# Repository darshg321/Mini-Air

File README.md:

# Mini-Air

Mini-Air is a DIY FPV drone!
it features:
- a custom flight controller supporting Betaflight
- an ESC supporting Bluejay firmware
- ELRS protocol
- an analog camera
- GPS

the custom flight controller has an on-board OSD, IMU, Barometer, and SPI Flash

i made this project to learn how flight controllers and drones work, and because i want to fly a cool fpv drone. the project is optimized to support the features of all the latest fpv software available. all components are analog to reduce latency, and because 480p drone video with osd in general is really aesthetic. with a 2s lipo and a 2-inch propellers, it leans heavily towards speed rather than range or flight time. the vtx, gps, reciever, and esc are all modular, and so can be swapped with different parts if needed. note that the CAD is simplified to just show the rough connection, i am using a bought frame which will allow for screwing in components.

## Poster (Zine)

## Flight Controller Render

## CAD Render

## PCB

## Schematic

## CAD

https://cad.onshape.com/documents/986fb99af7814b930792b89c/w/8ba981f62ca8b18288746bfa/e/dd69b1ef7cccc17bc086fed8?renderMode=0&uiState=6a3726ba5f00d66196d8cb0d

## Assembly:

1. mount ESC and FC to frame and screw in
2. mount propeller to motor and screw in to frame
3. solder camera, vtx, gps, reciever to flight controller
4. mount camera to front of frame, screw in other components to the back
5. flash betaflight firmware by connecting to FC with a STLINK
6. connect battery and radio controller
7. fly!

## BOM

|Item:                                       |Link:                                                                          |Price (CAD):|FIELD4|FIELD5 |Weight (g)|
|--------------------------------------------|-------------------------------------------------------------------------------|------------|------|-------|----------|
|FC PCB                                      |                                                                               |2.83        |      |       |3.9       |
|FC PCBA                                     |                                                                               |236.5       |      |       |          |
|Frame                                       |https://epicfpv.ca/products/hglrc-talon-frame-black                            |45.31       |      |       |46        |
|AneegFpv 45A ESC                            |https://www.aliexpress.com/item/1005009952151526.html                          |32.99       |      |       |13        |
|4x HappyModel EX1103S 1103 7000KV           |https://www.aliexpress.com/item/1005006105578345.html                          |44.59       |      |       |15.2      |
|Propellers                                  |https://www.aliexpress.com/item/1005006966517627.html                          |6.49        |      |       |3.52      |
|CADDX Ant FPV Lite Camera                   |https://www.aliexpress.com/item/1005009014299964.html                          |19.87       |      |       |2         |
|Zeus nano 350mW VTX                         |https://www.aliexpress.com/item/1005008558004179.html                          |35.58       |      |       |2.4       |
|Foxeer Lollipop 3 Micro Omni V4 RHCP Antenna|https://www.aliexpress.com/item/4001191873858.html                             |16.89       |      |       |4.7       |
|HappyModel 2.4G ELRS EP2 Reciever           |https://www.aliexpress.com/item/1005009851731060.html                          |19.18       |      |       |0.41      |
|NewBeeDrone M10Q Micro GPS Module           |https://newbeedrone.com/products/newbeedrone-m10q-micro-gps-module-with-compass|27.80       |      |       |2.61      |
|LiteRadio 2 ELRS                            |https://www.aliexpress.com/item/1005011890268150.html                          |31.18       |      |       |          |
|x4 2S 450mAh 80C lipo battery               |https://www.aliexpress.com/item/1005006138925891.html                          |37.99       |      |       |30        |
|                                            |                                                                               |            |      |       |          |
|                                            |Total USD                                                                      |401.18      |      |Weight:|123.74    |

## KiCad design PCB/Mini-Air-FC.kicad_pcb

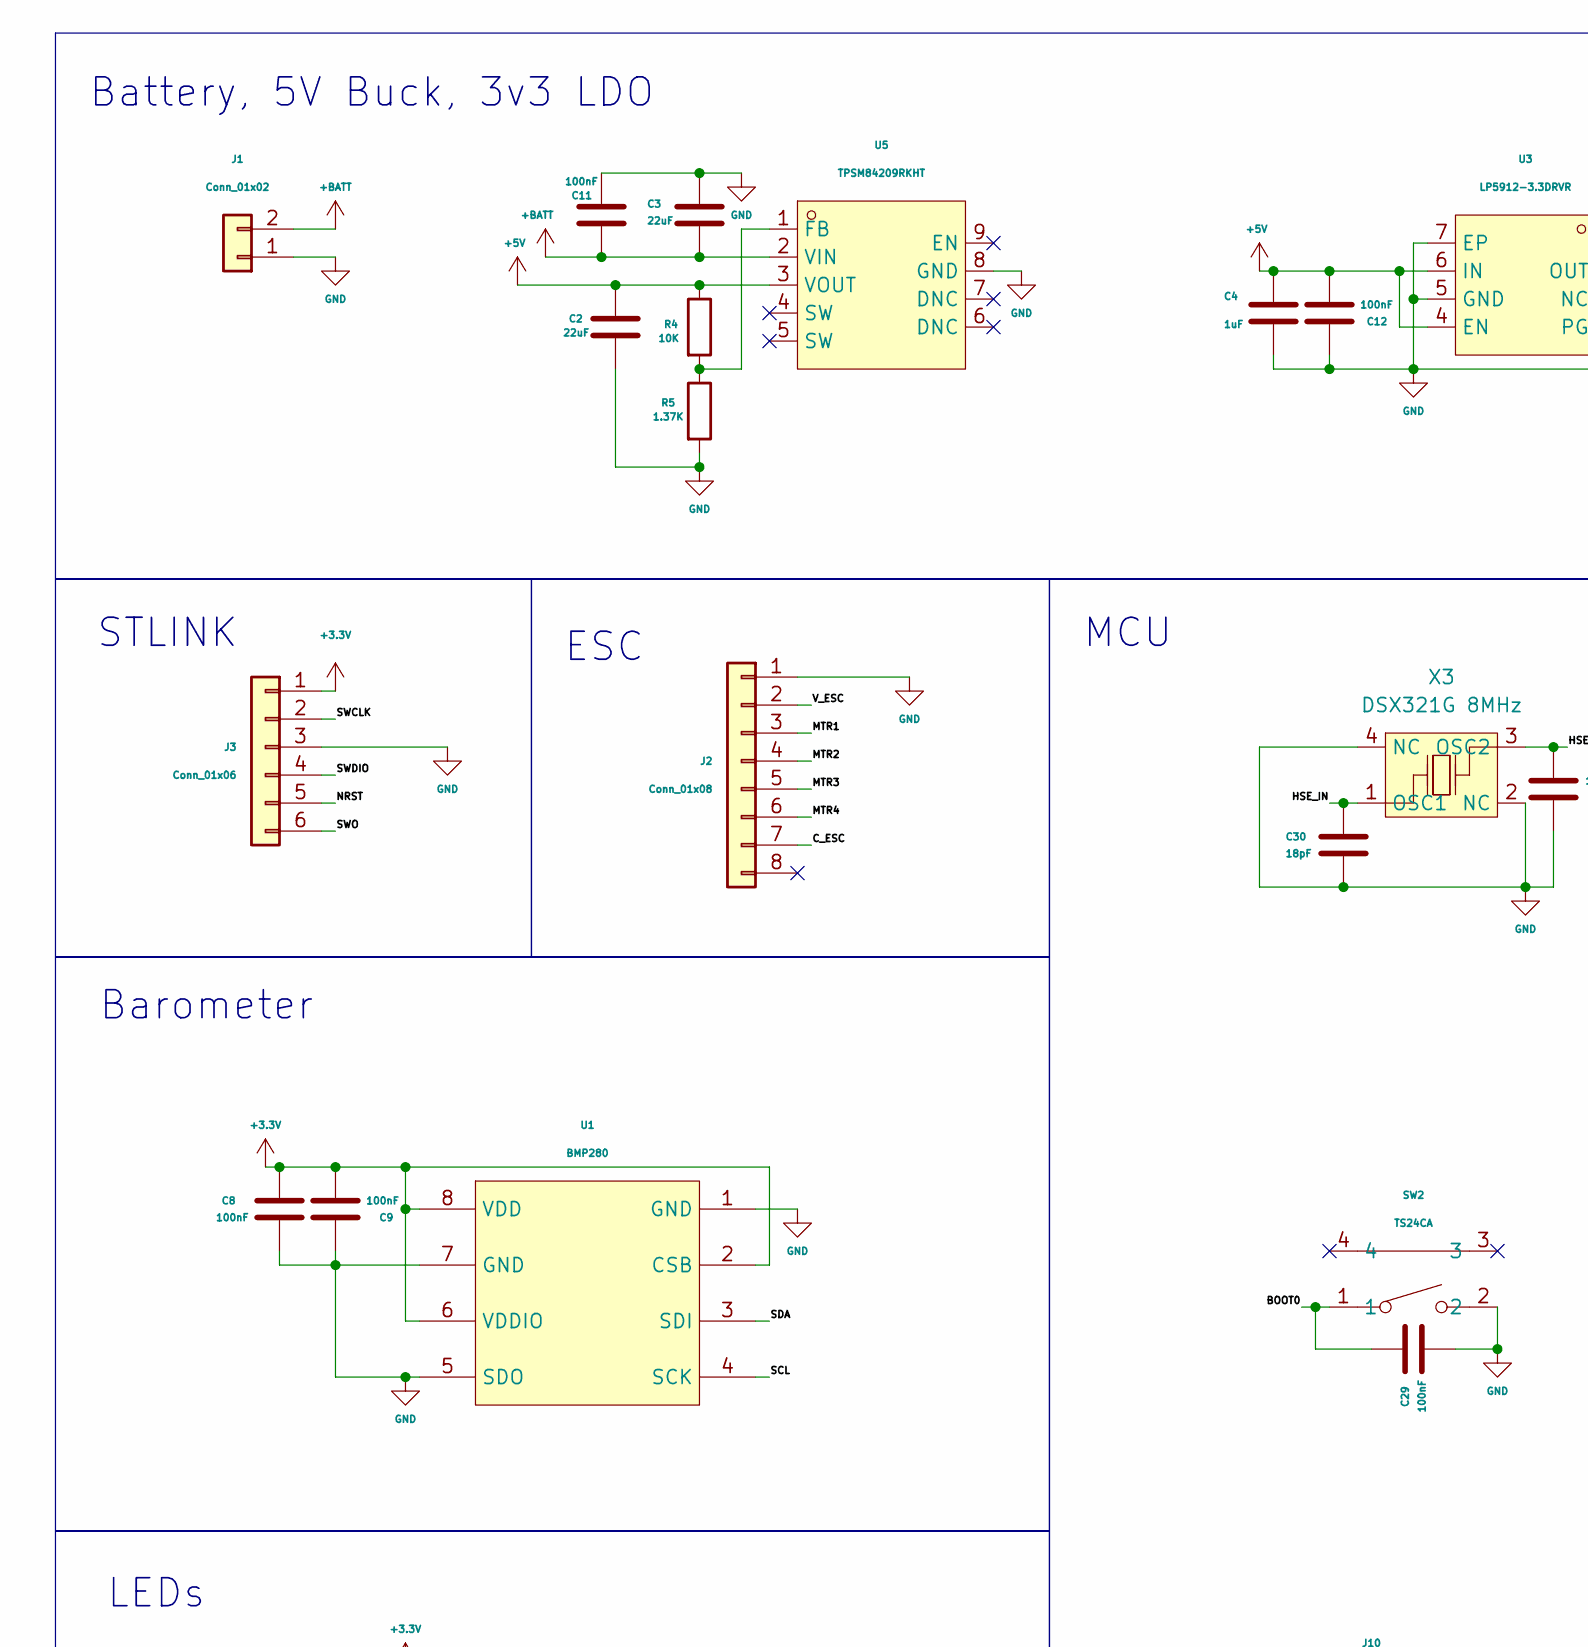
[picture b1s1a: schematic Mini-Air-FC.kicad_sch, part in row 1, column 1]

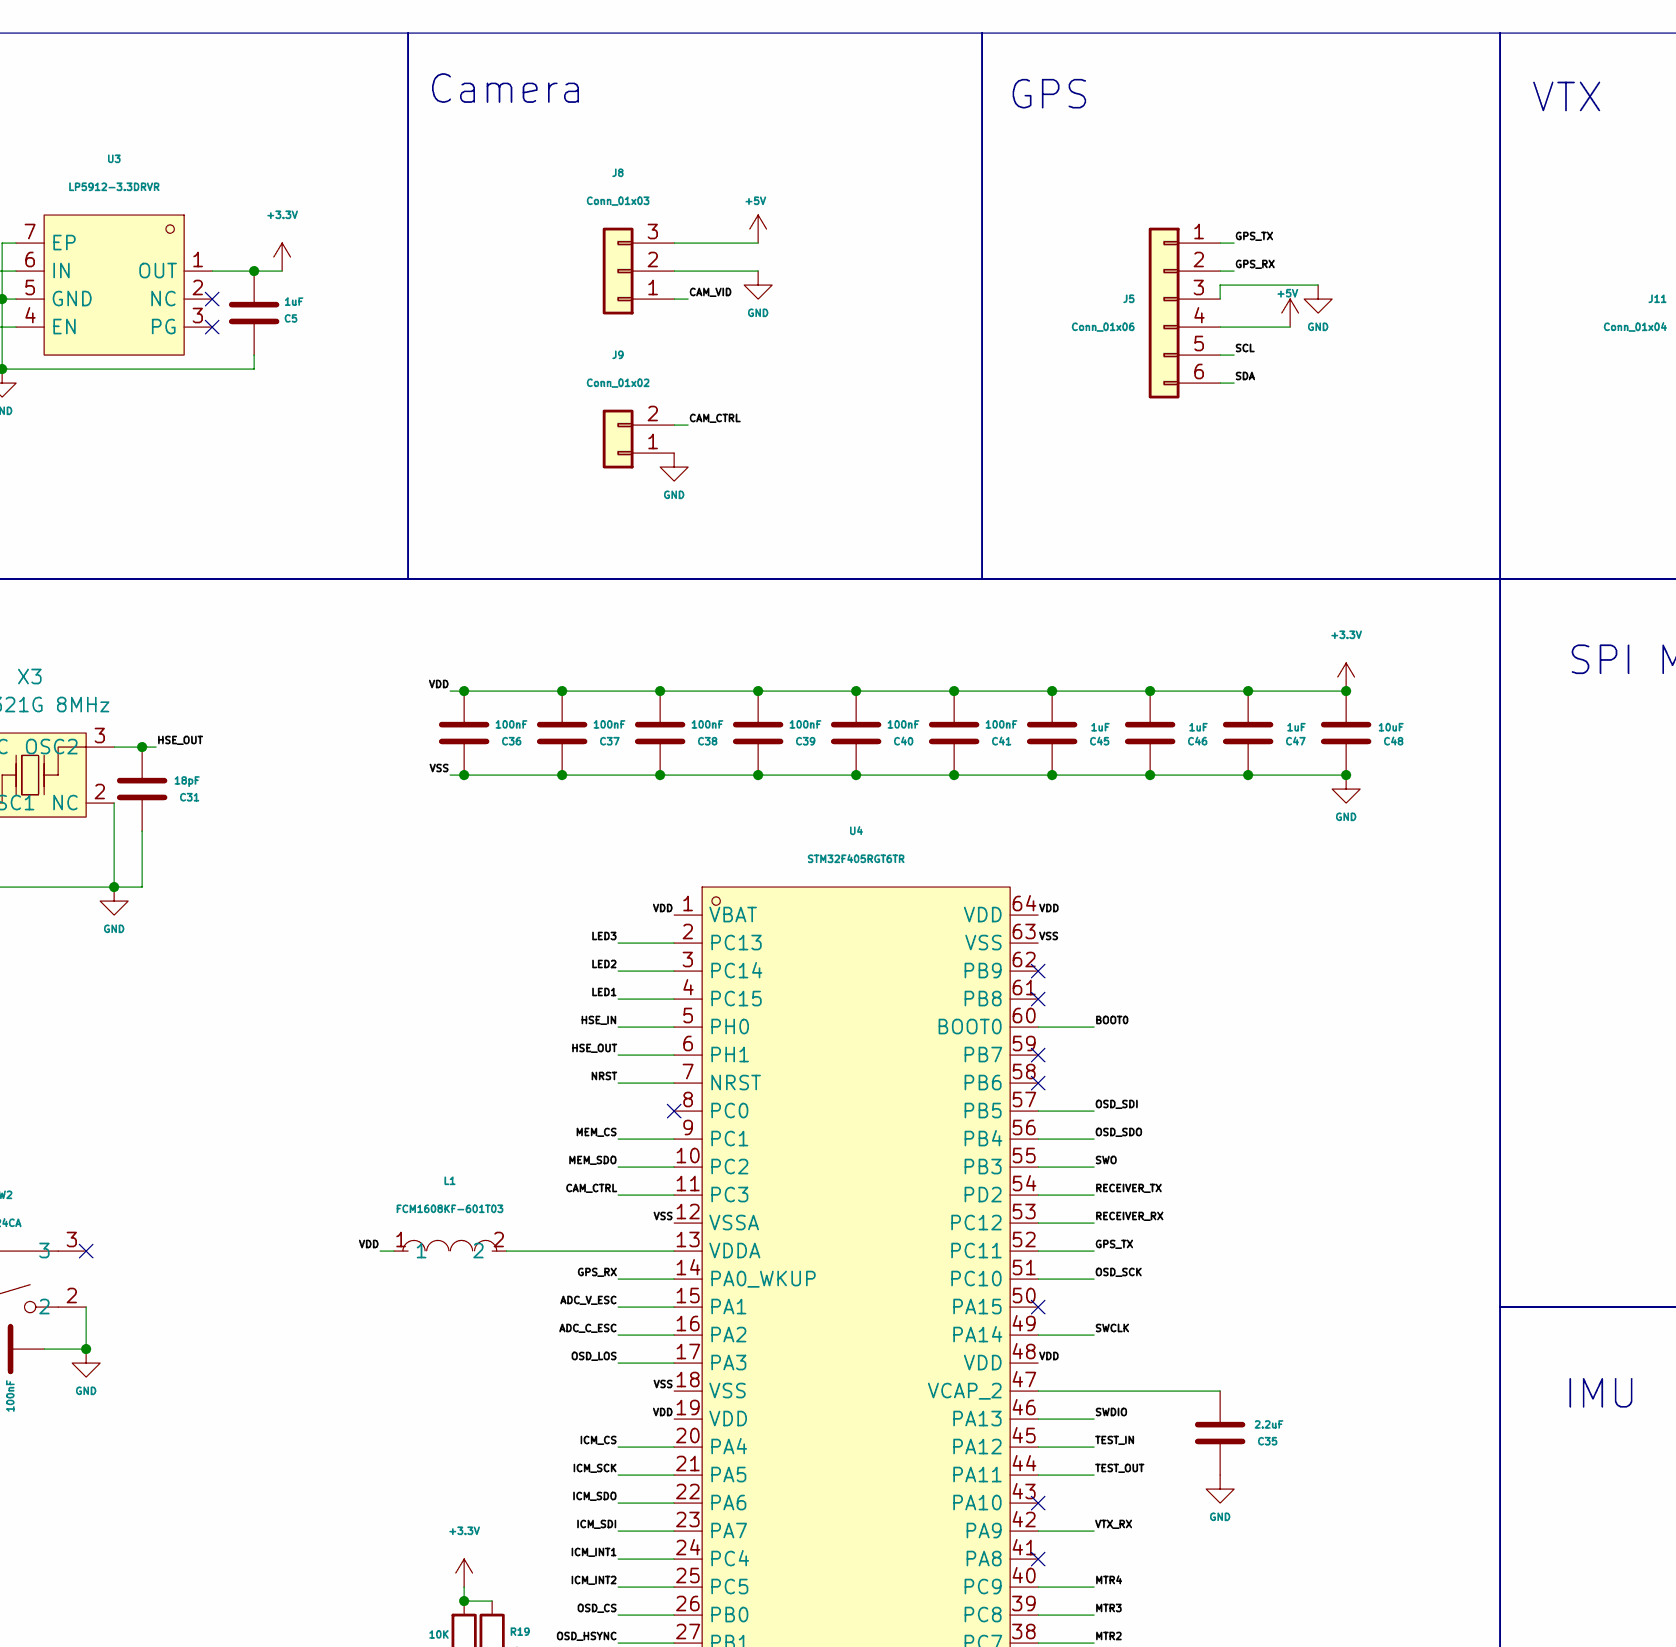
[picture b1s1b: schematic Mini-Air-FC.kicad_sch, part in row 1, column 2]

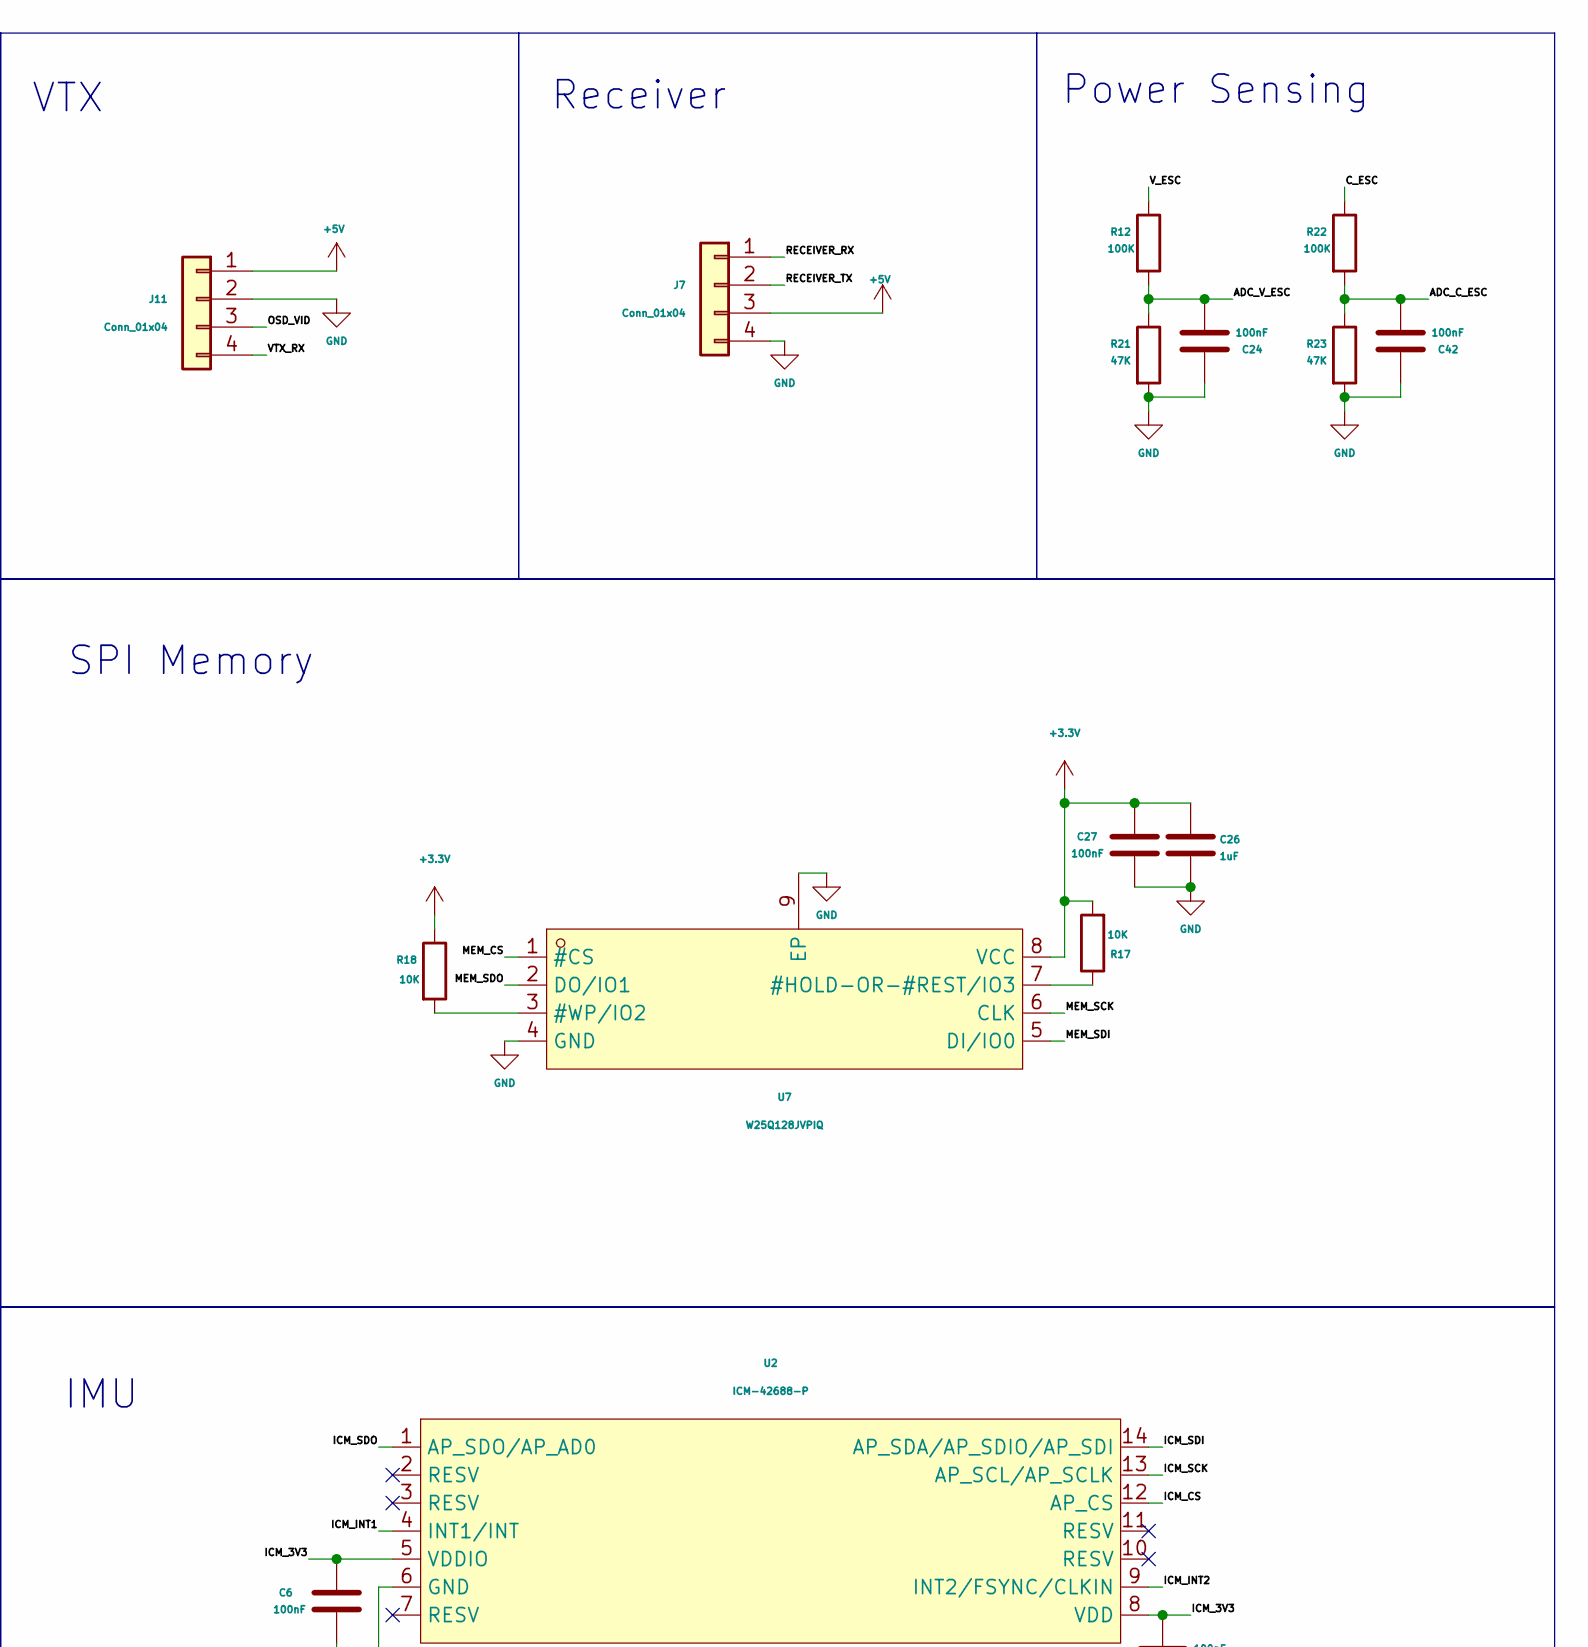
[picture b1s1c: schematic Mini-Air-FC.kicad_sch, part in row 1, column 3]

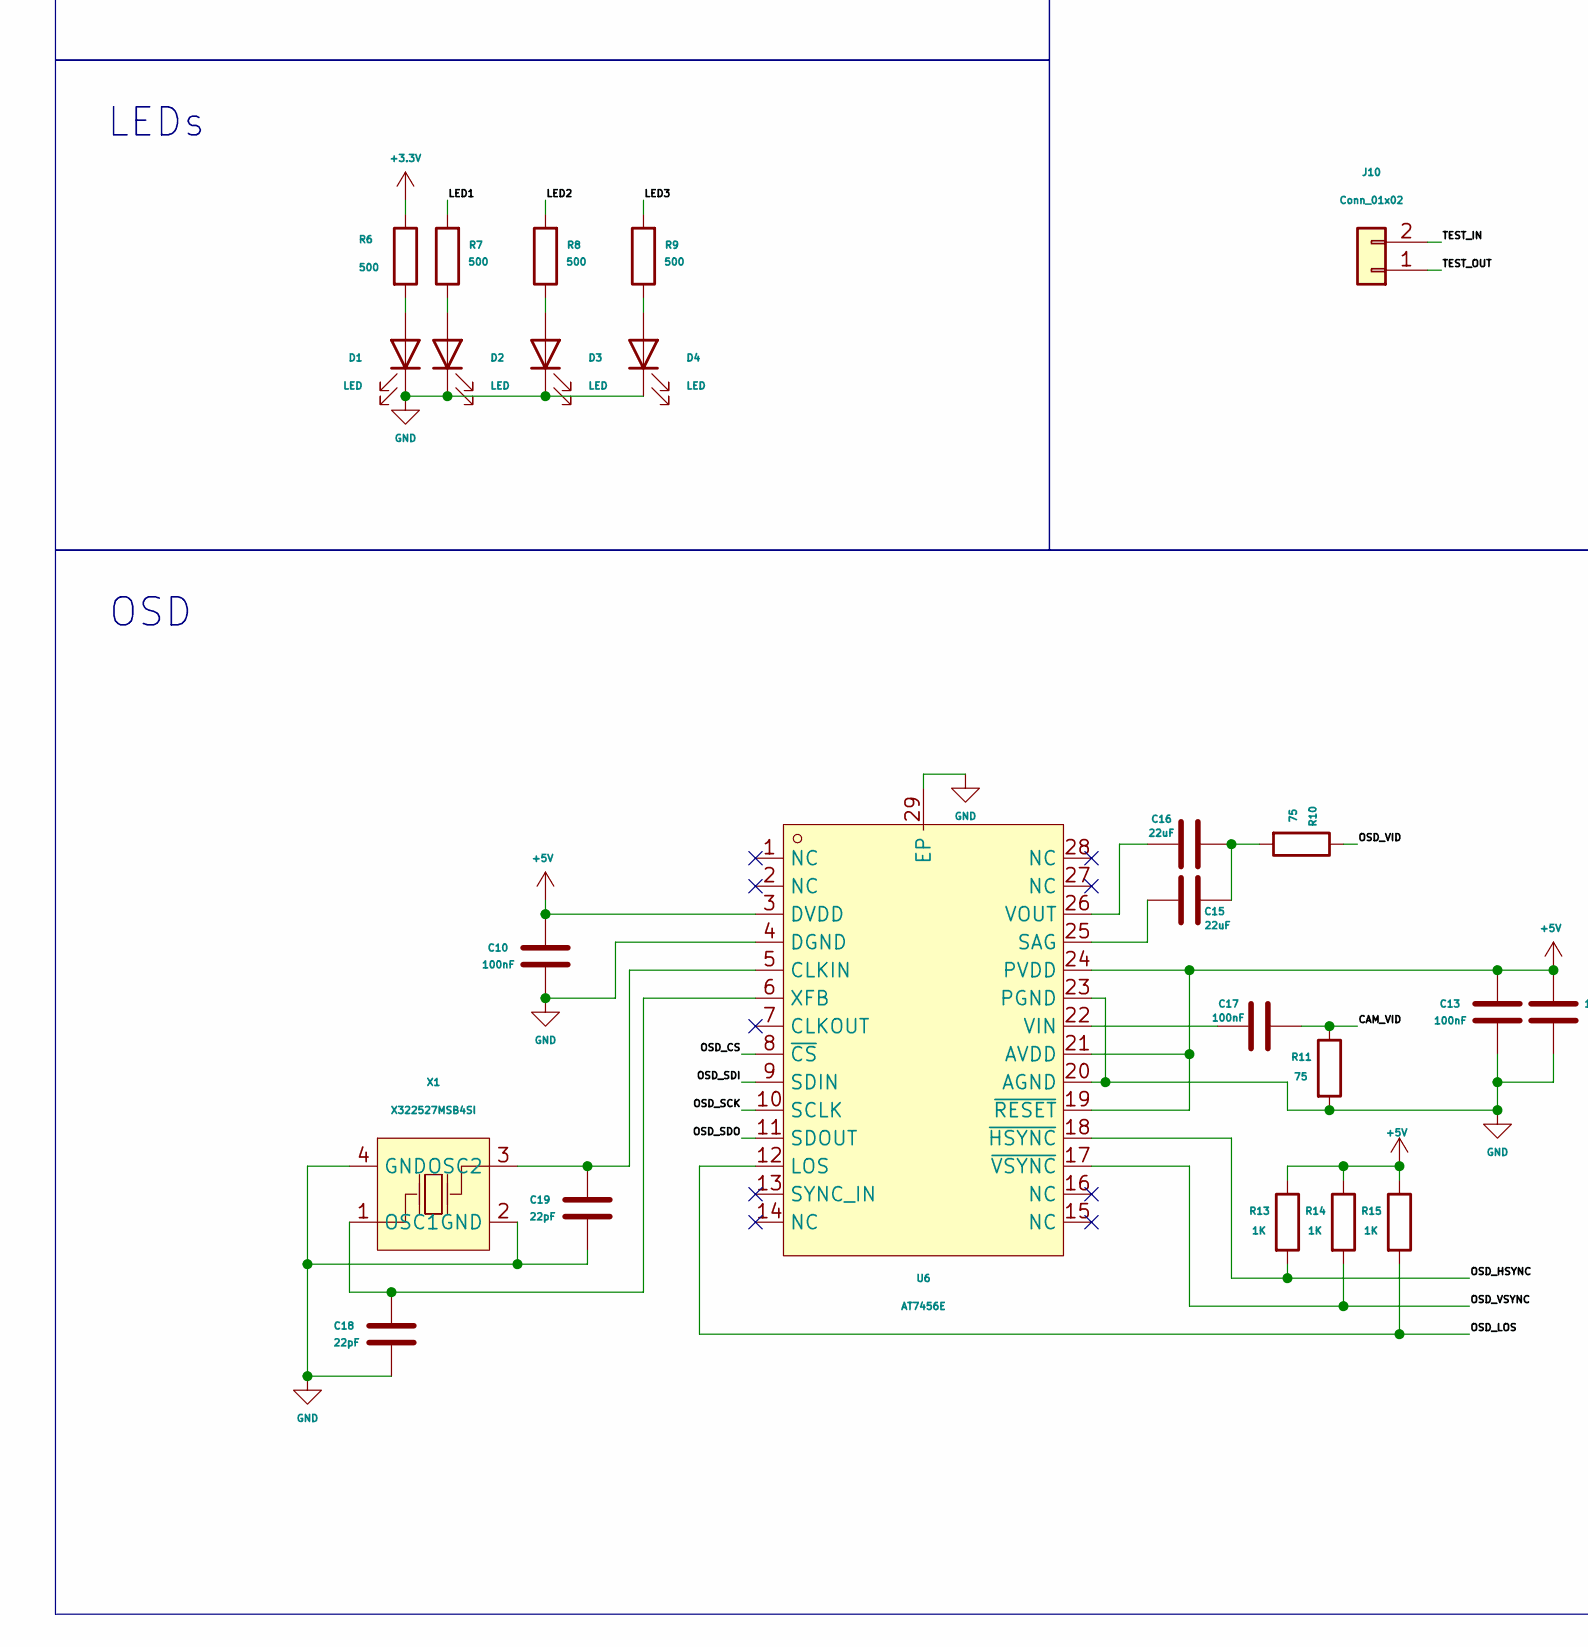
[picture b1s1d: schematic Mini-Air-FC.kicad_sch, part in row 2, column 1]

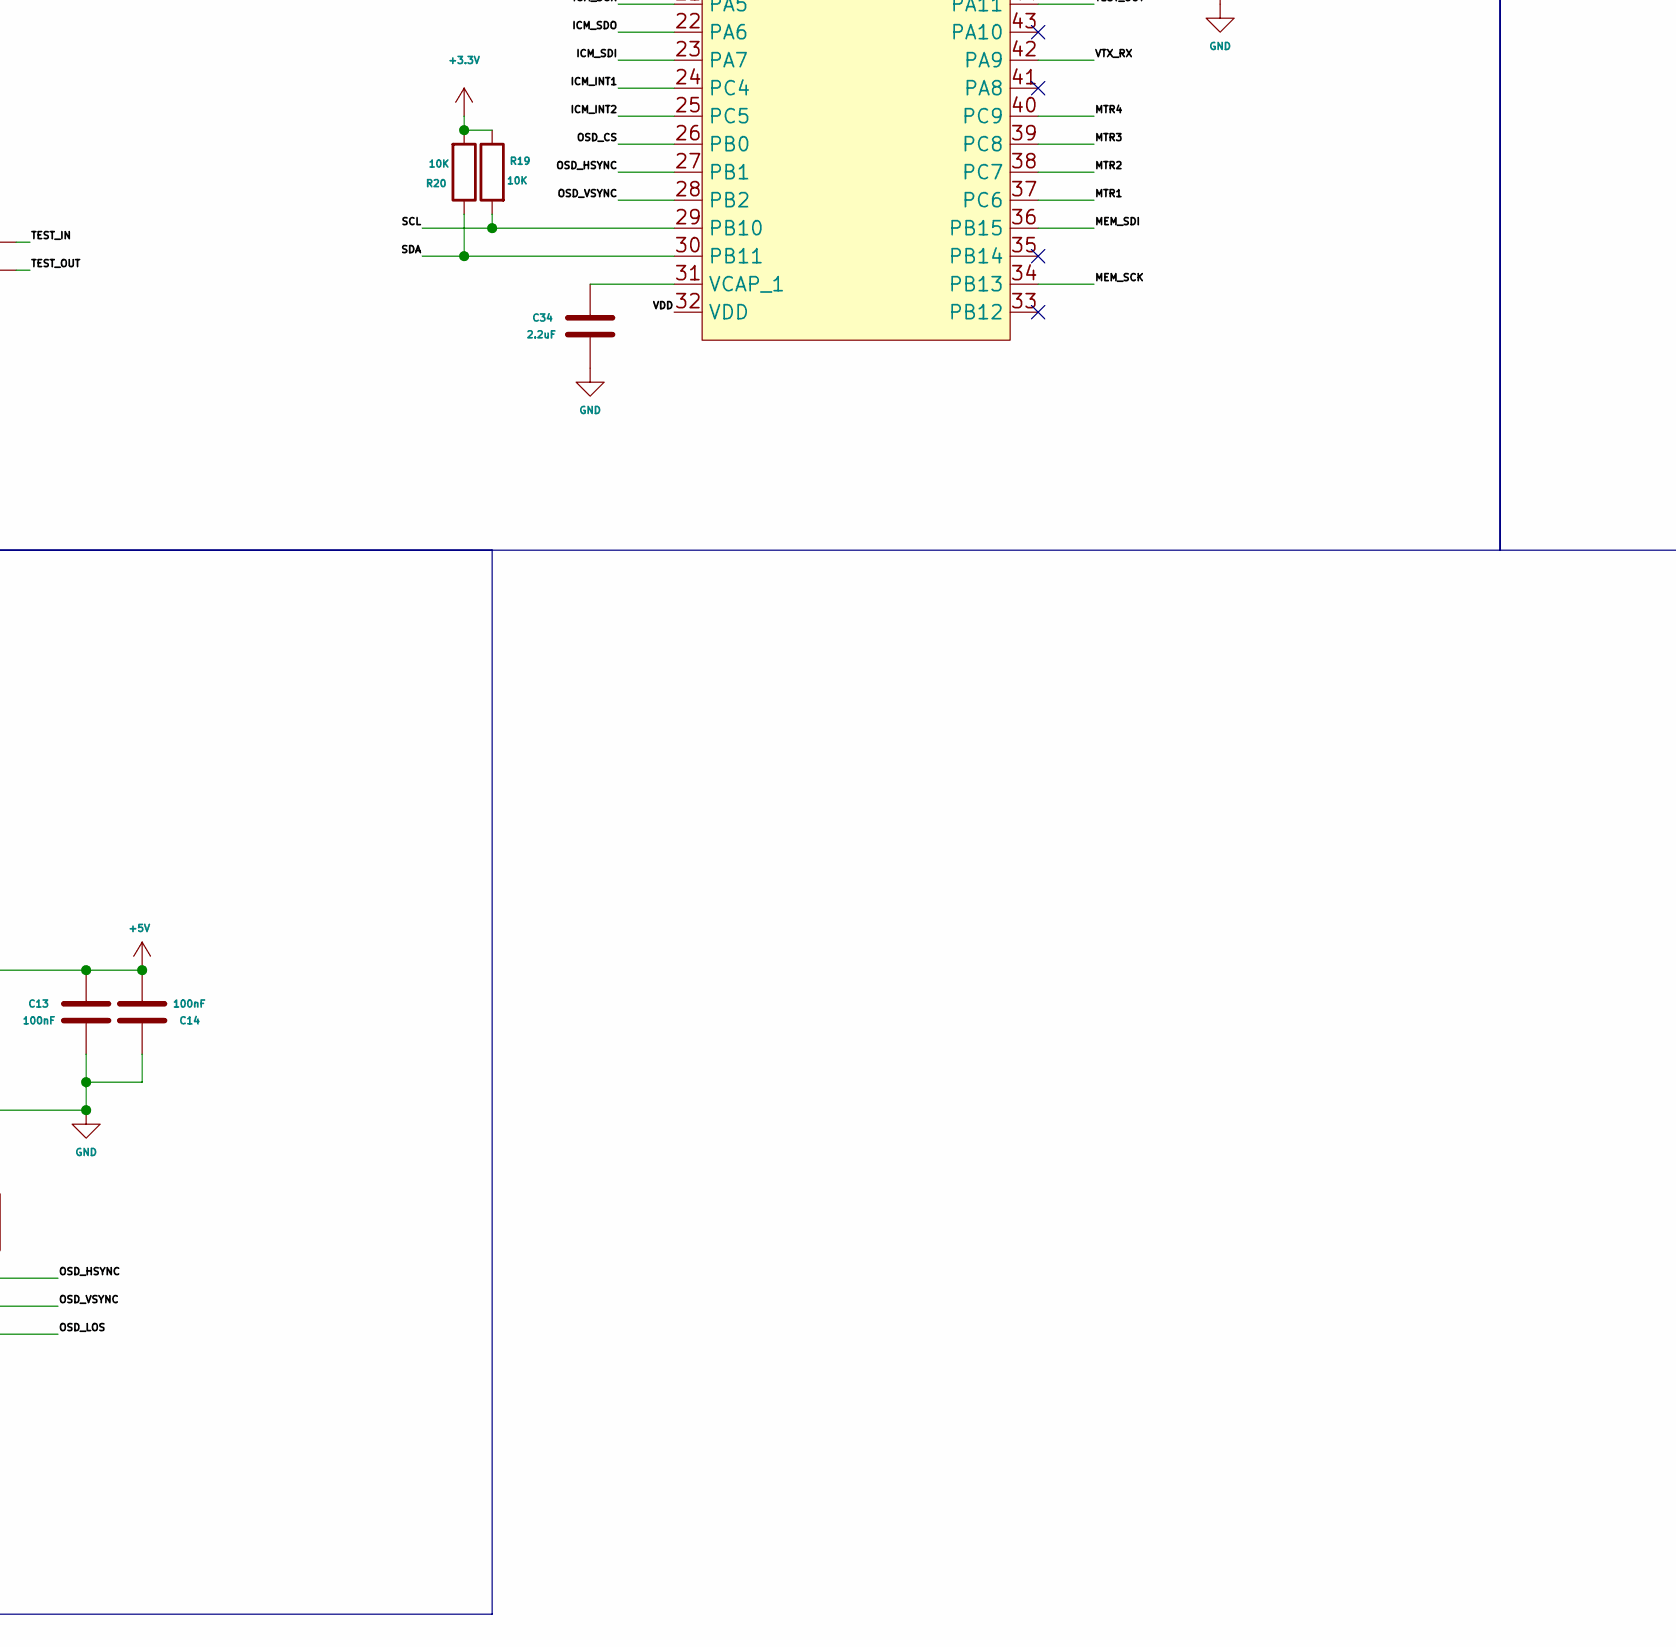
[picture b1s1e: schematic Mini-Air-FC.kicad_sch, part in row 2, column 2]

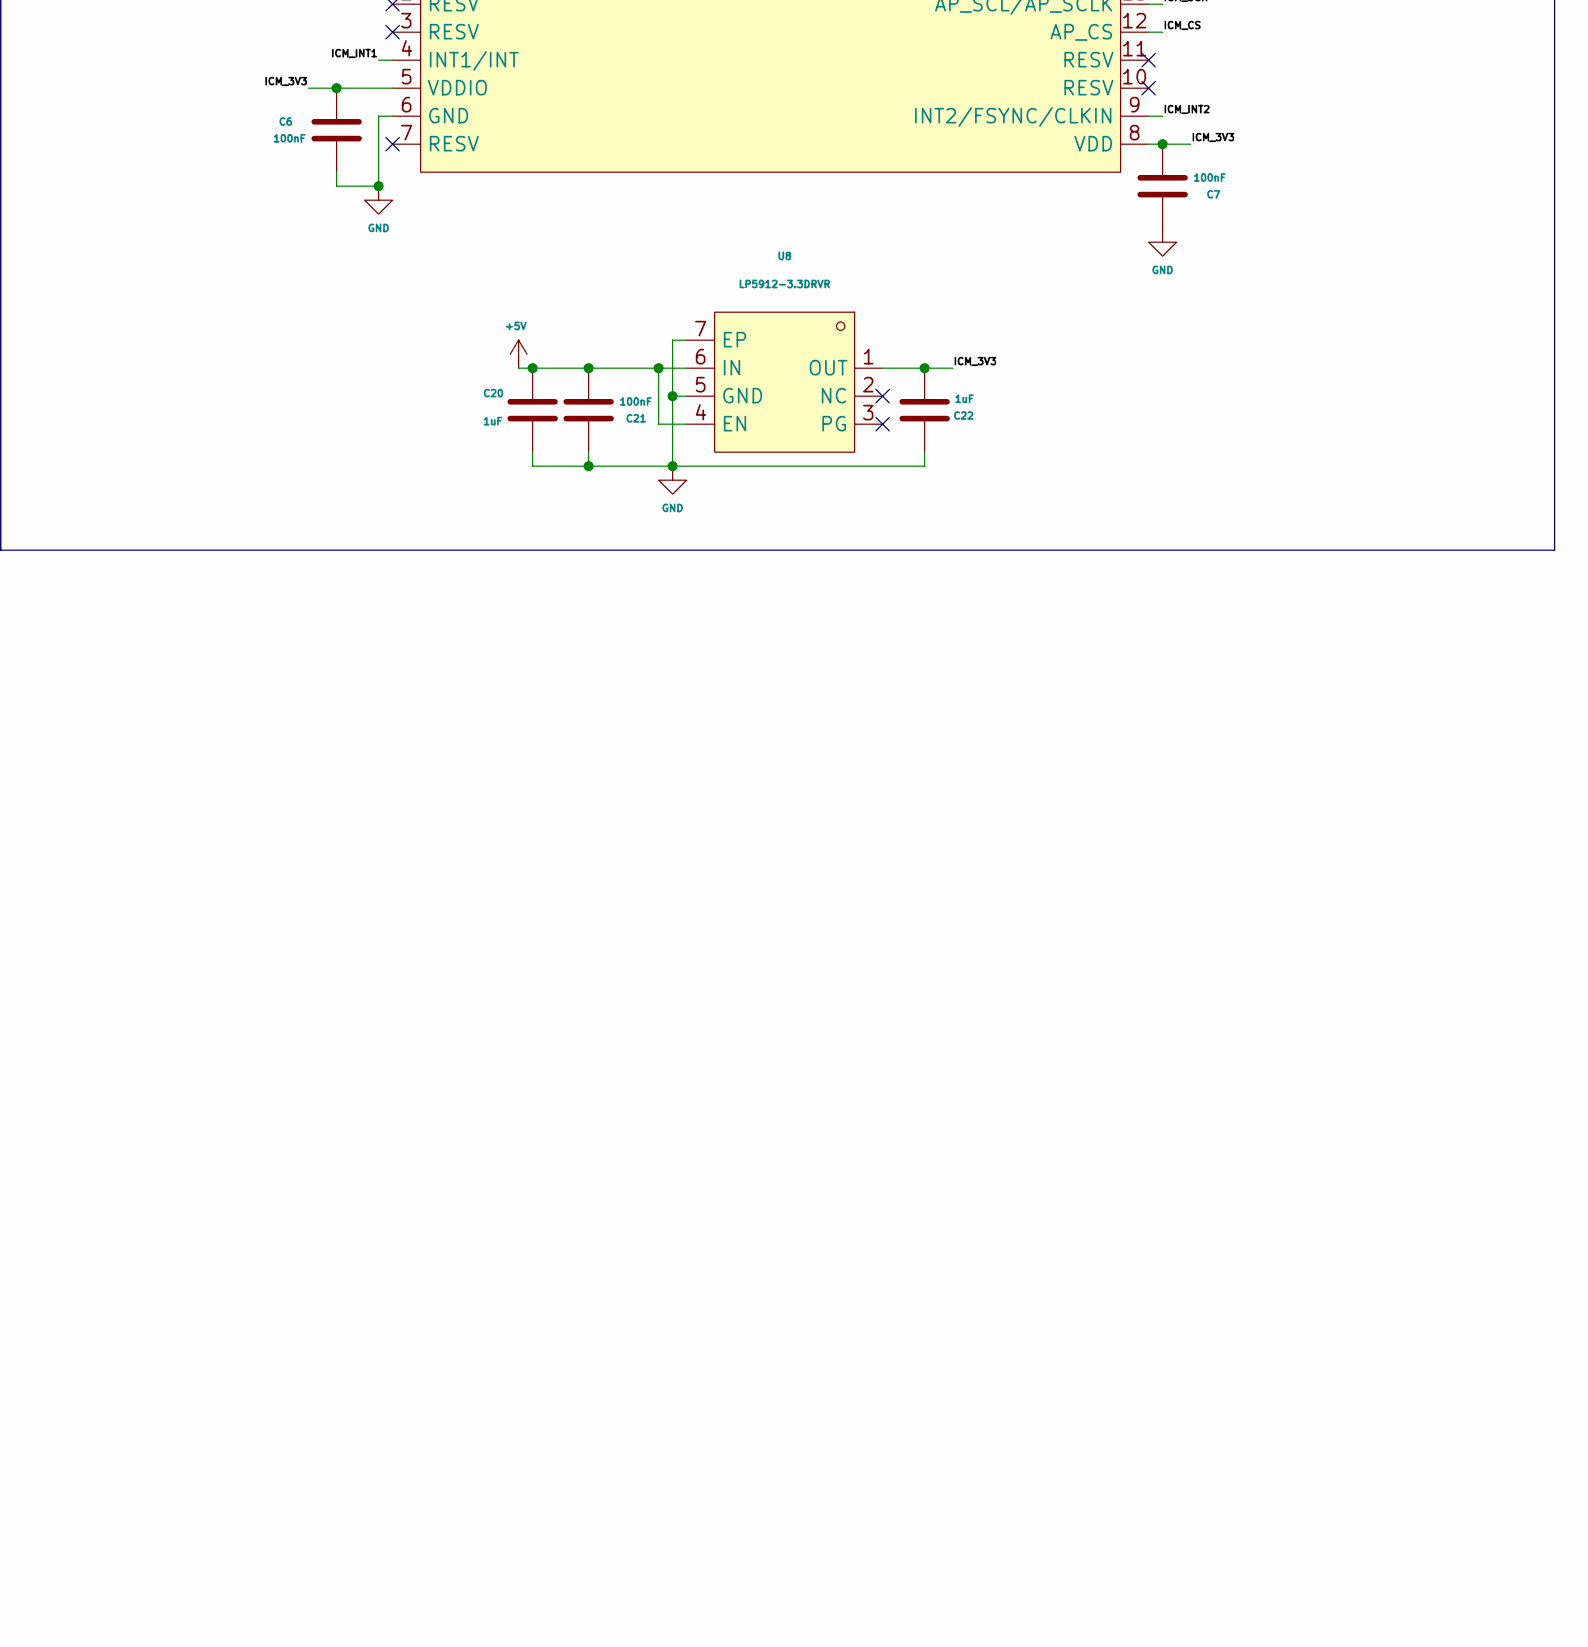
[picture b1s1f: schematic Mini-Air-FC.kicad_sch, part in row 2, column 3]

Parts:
C2, C3, C15, C16: 22uF; C_0805_2012Metric
C4, C5, C20, C22, C26, C45, C46, C47: 1uF; C_0402_1005Metric
C6, C7, C8, C9, C10, C11, C12, C13, C14, C17, C21, C24, C27, C29, C36, C37, C38, C39, C40, C41, C42: 100nF; C_0201_0603Metric
C18, C19: 22pF; C_0201_0603Metric
C30, C31: 18pF; C_0201_0603Metric
C34, C35: 2.2uF; C_0402_1005Metric
C48: 10uF; C_0805_2012Metric
D1, D2, D3, D4: LED; LED_0402_1005Metric
J1, J9, J10: Conn_01x02; PinHeader_1x02_P1.00mm_Vertical
J2: Conn_01x08; JST_SH_SM08B-SRSS-TB_1x08-1MP_P1.00mm_Horizontal
J3, J5: Conn_01x06; PinHeader_1x06_P1.00mm_Vertical
J7, J11: Conn_01x04; PinHeader_1x04_P1.00mm_Vertical
J8: Conn_01x03; PinHeader_1x03_P1.00mm_Vertical
L1: FCM1608KF-601T03; L0603; MPN FCM1608KF-601T03; LCSC Part C141723
R4, R17, R18, R19, R20: 10K; R_0201_0603Metric
R5: 1.37K; R_0201_0603Metric
R6, R7, R8, R9: 500; R_0201_0603Metric
R10, R11: 75; R_0201_0603Metric
R12, R22: 100K; R_0201_0603Metric
R13, R14, R15: 1K; R_0201_0603Metric
R21, R23: 47K; R_0201_0603Metric
SW2: TS24CA; SW-SMD_2P-TS24CA; MPN TS24CA; LCSC Part C393942
U1: BMP280; LGA-8_L2.5-W2.0-P0.65_AMP6127; MPN BMP280; LCSC Part C83291
U2: ICM-42688-P; LGA-14_L3.0-W2.5-P0.50-TL; MPN ICM-42688-P; LCSC Part C1850418
U3, U8: LP5912-3.3DRVR; WSON-6_L2.0-W2.0-P0.65-TL-EP; MPN LP5912-3.3DRVR; LCSC Part C524780
U4: STM32F405RGT6TR; LQFP-64_L10.0-W10.0-P0.50-LS12.0-BL; MPN STM32F405RGT6TR; LCSC Part C2054141
U5: TPSM84209RKHT; QFN-9_L4.4-W4.0-P0.85-YTL; MPN TPSM84209RKHT; LCSC Part C2836944
U6: AT7456E; TSSOP-28_L9.7-W4.4-P0.65-LS6.4-BL-EP-2; MPN AT7456E; LCSC Part C82351
U7: W25Q128JVPIQ; WSON-8_L6.0-W5.0-P1.27-BL-EP; MPN W25Q128JVPIQ; LCSC Part C190862
X1: X322527MSB4SI; CRYSTAL-SMD_4P-L3.2-W2.5-BL-1; MPN X322527MSB4SI; LCSC Part C9008
X3: DSX321G 8MHz; CRYSTAL-SMD_4P-L3.2-W2.5-BL-1; MPN 1C208000BC0R; LCSC Part C57131

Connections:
+3.3V: C5.2, C8.1, C9.2, C26.1, C27.1, C36.2, C37.2, C38.2, C39.2, C40.2, C41.2, C45.2, C46.2, C47.2, C48.2, J3.1, L1.1, R6.1, R17.2, R18.1, R19.1, R20.2, U1.2 (CSB), U1.6 (VDDIO), U1.8 (VDD), U3.1 (OUT), U4.1 (VBAT), U4.19 (VDD), U4.32 (VDD), U4.48 (VDD), U4.64 (VDD), U7.8 (VCC)
+5V: C2.1, C4.1, C10.1, C12.2, C13.1, C14.2, C20.1, C21.2, J5.4, J7.3, J8.3, J11.1, R4.1, R13.1, R14.1, R15.1, U3.4 (EN), U3.6 (IN), U5.3 (VOUT), U6.3 (DVDD), U6.19 (~RESET), U6.21 (AVDD), U6.24 (PVDD), U8.4 (EN), U8.6 (IN)
+BATT: C3.2, C11.1, J1.2, U5.2 (VIN)
/ADC_C_ESC: C42.2, R22.2, R23.1, U4.16 (PA2)
/ADC_V_ESC: C24.2, R12.2, R21.1, U4.15 (PA1)
/BOOT0: C29.1, SW2.1, U4.60 (BOOT0)
/CAM_CTRL: J9.2, U4.11 (PC3)
/CAM_VID: C17.2, J8.1, R11.1
/C_ESC: J2.7, R22.1
/GPS_RX: J5.2, U4.14 (PA0_WKUP)
/GPS_TX: J5.1, U4.52 (PC11)
/HSE_IN: C30.1, U4.5 (PH0), X3.1 (OSC1)
/HSE_OUT: C31.2, U4.6 (PH1), X3.3 (OSC2)
/ICM_3V3: C6.1, C7.2, C22.2, U2.5 (VDDIO), U2.8 (VDD), U8.1 (OUT)
/ICM_CS: U2.12 (AP_CS), U4.20 (PA4)
/ICM_INT1: U2.4 (INT1/INT), U4.24 (PC4)
/ICM_INT2: U2.9 (INT2/FSYNC/CLKIN), U4.25 (PC5)
/ICM_SCK: U2.13 (AP_SCL/AP_SCLK), U4.21 (PA5)
/ICM_SDI: U2.14 (AP_SDA/AP_SDIO/AP_SDI), U4.23 (PA7)
/ICM_SDO: U2.1 (AP_SDO/AP_AD0), U4.22 (PA6)
/LED1: R7.2, U4.4 (PC15)
/LED2: R8.2, U4.3 (PC14)
/LED3: R9.2, U4.2 (PC13)
/MEM_CS: U4.9 (PC1), U7.1 (#CS)
/MEM_SCK: U4.34 (PB13), U7.6 (CLK)
/MEM_SDI: U4.36 (PB15), U7.5 (DI/IO0)
/MEM_SDO: U4.10 (PC2), U7.2 (DO/IO1)
/MTR1: J2.3, U4.37 (PC6)
/MTR2: J2.4, U4.38 (PC7)
/MTR3: J2.5, U4.39 (PC8)
/MTR4: J2.6, U4.40 (PC9)
/NRST: J3.5, U4.7 (NRST)
/OSD_CS: U4.26 (PB0), U6.8 (~CS)
/OSD_HSYNC: R13.2, U4.27 (PB1), U6.18 (~HSYNC)
/OSD_LOS: R15.2, U4.17 (PA3), U6.12 (LOS)
/OSD_SCK: U4.51 (PC10), U6.10 (SCLK)
/OSD_SDI: U4.57 (PB5), U6.9 (SDIN)
/OSD_SDO: U4.56 (PB4), U6.11 (SDOUT)
/OSD_VID: J11.3, R10.1
/OSD_VSYNC: R14.2, U4.28 (PB2), U6.17 (~VSYNC)
/RECEIVER_RX: J7.1, U4.53 (PC12)
/RECEIVER_TX: J7.2, U4.54 (PD2)
/SCL: J5.5, R19.2, U1.4 (SCK), U4.29 (PB10)
/SDA: J5.6, R20.1, U1.3 (SDI), U4.30 (PB11)
/SWCLK: J3.2, U4.49 (PA14)
/SWDIO: J3.4, U4.46 (PA13)
/SWO: J3.6, U4.55 (PB3)
/TEST_IN: J10.2, U4.45 (PA12)
/TEST_OUT: J10.1, U4.44 (PA11)
/VTX_RX: J11.4, U4.42 (PA9)
/V_ESC: J2.2, R12.1
GND: C2.2, C3.1, C4.2, C5.1, C6.2, C7.1, C8.2, C9.1, C10.2, C11.2, C12.1, C13.2, C14.1, C18.2, C19.2, C20.2, C21.1, C22.1, C24.1, C26.2, C27.2, C29.2, C30.2, C31.1, C34.2, C35.1, C36.1, C37.1, C38.1, C39.1, C40.1, C41.1, C42.1, C45.1, C46.1, C47.1, C48.1, D1.1 (K), D2.1 (K), D3.1 (K), D4.1 (K), J1.1, J2.1, J3.3, J5.3, J7.4, J8.2, J9.1, J11.2, R5.2, R11.2, R21.2, R23.2, SW2.2, U1.1 (GND), U1.5 (SDO), U1.7 (GND), U2.6 (GND), U3.5 (GND), U3.7 (EP), U4.12 (VSSA), U4.18 (VSS), U4.63 (VSS), U5.8 (GND), U6.4 (DGND), U6.20 (AGND), U6.23 (PGND), U6.29 (EP), U7.4 (GND), U7.9 (EP), U8.5 (GND), U8.7 (EP), X1.2 (GND), X1.4 (GND), X3.2 (NC), X3.4 (NC)
unnamed: C15.2, C16.1, R10.2
unnamed: D1.2 (A), R6.2
unnamed: D2.2 (A), R7.1
unnamed: D3.2 (A), R8.1
unnamed: D4.2 (A), R9.1
unnamed: C34.1, U4.31 (VCAP_1)
unnamed: C35.2, U4.47 (VCAP_2)
unnamed: L1.2, U4.13 (VDDA)
unnamed: R4.2, R5.1, U5.1 (FB)
unnamed: C19.1, U6.5 (CLKIN), X1.3 (OSC2)
unnamed: C15.1, U6.25 (SAG)
unnamed: C17.1, U6.22 (VIN)
unnamed: C16.2, U6.26 (VOUT)
unnamed: C18.1, U6.6 (XFB), X1.1 (OSC1)
unnamed: R17.1, U7.7 (#HOLD-OR-#REST/IO3)
unnamed: R18.2, U7.3 (#WP/IO2)

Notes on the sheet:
IMU
SPI Memory
ESC
Camera
Barometer
GPS
VTX
MCU
LEDs
OSD
Power Sensing
Battery, 5V Buck, 3v3 LDO
STLINK
Receiver
